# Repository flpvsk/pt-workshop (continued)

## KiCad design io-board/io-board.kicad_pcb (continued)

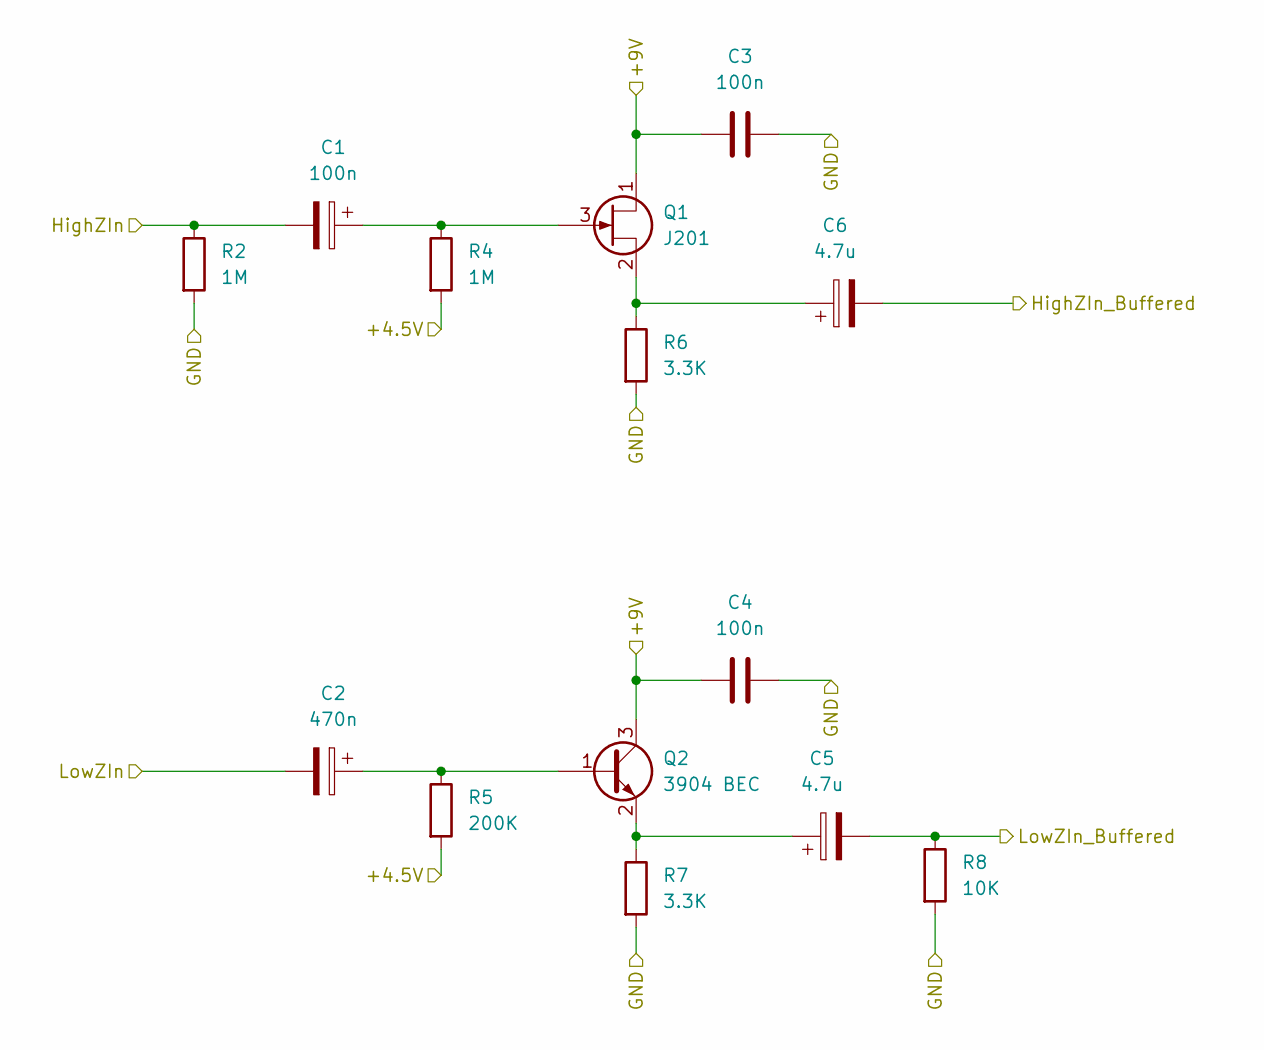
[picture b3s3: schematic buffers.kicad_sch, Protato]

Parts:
C1: 100n; CP_Elec_4x5.4; LCSC C271438
C2: 470n; CP_Elec_4x5.4; LCSC C305350
C3, C4: 100n; C_0603_1608Metric_Pad1.08x0.95mm_HandSolder; LCSC C497032
C5, C6: 4.7u; CP_Elec_4x5.4; Mouser 710-865080540002
Q1: J201; SOT-23_Handsoldering; LCSC C891687
Q2: 3904 BEC; SOT-23_Handsoldering; LCSC C20526
R2, R4: 1M; R_0603_1608Metric_Pad0.98x0.95mm_HandSolder; LCSC C105578
R5: 200K; R_0603_1608Metric_Pad0.98x0.95mm_HandSolder; LCSC C25811
R6, R7: 3.3K; R_0603_1608Metric_Pad0.98x0.95mm_HandSolder; LCSC C22978
R8: 10K; R_0603_1608Metric_Pad0.98x0.95mm_HandSolder; LCSC C25804

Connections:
/+4.5V: R4.2, R5.2; also elsewhere on the board
/Return: C2.2; also elsewhere on the board
/ReturnBuf: C5.2, R8.1; also elsewhere on the board
/Send: C1.2, R2.1; also elsewhere on the board
/SendBuf: C6.2; also elsewhere on the board
/Von: C3.1, C4.1, Q1.1 (D), Q2.3 (C); also elsewhere on the board
GND: C3.2, C4.2, R2.2, R6.2, R7.2, R8.2; also elsewhere on the board
unnamed: C1.1, Q1.3 (G), R4.1
unnamed: C2.1, Q2.1 (B), R5.1
unnamed: C5.1, Q2.2 (E), R7.1
unnamed: C6.1, Q1.2 (S), R6.1

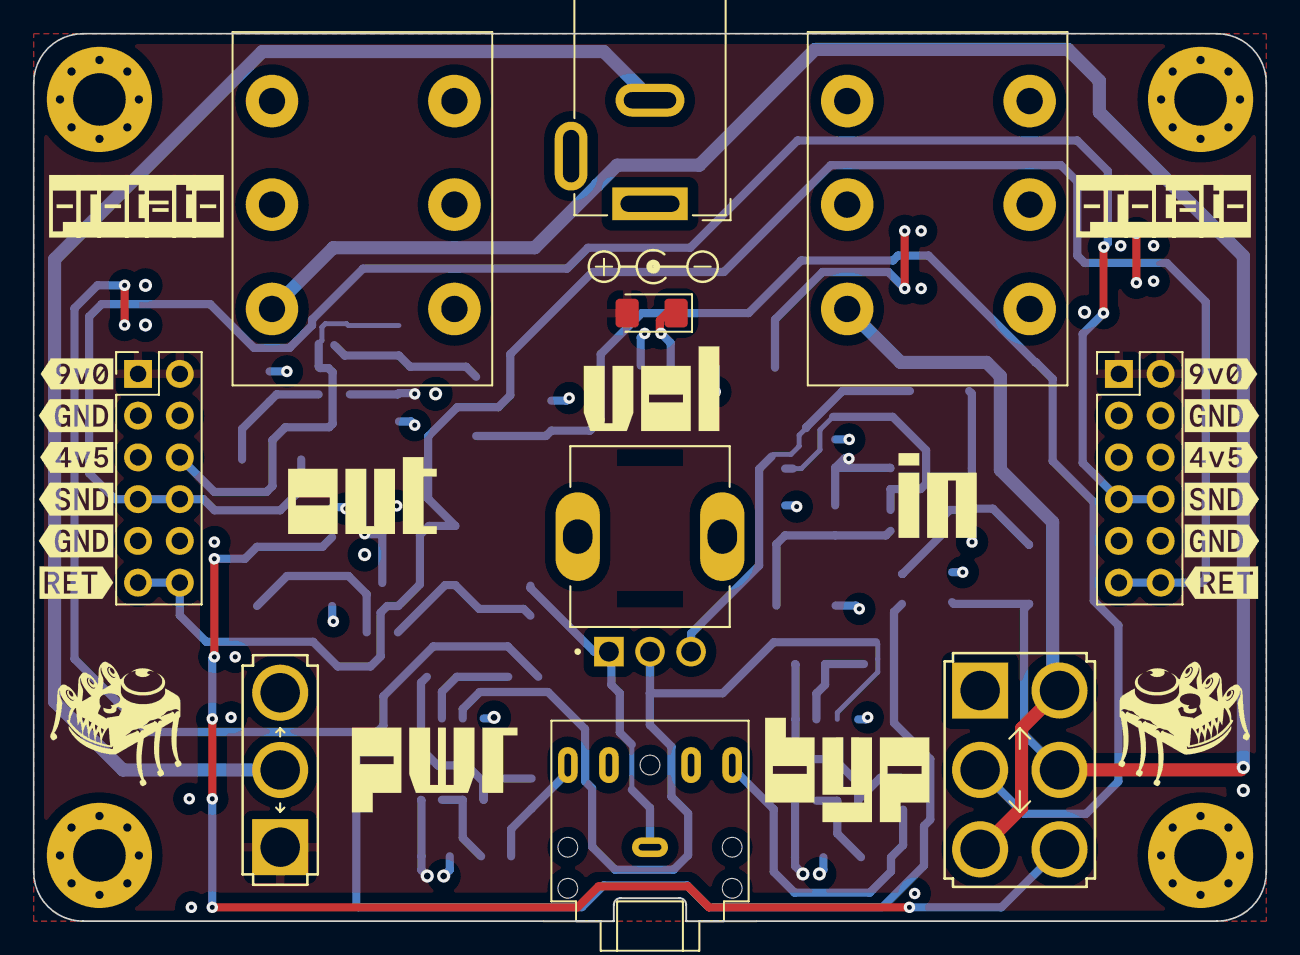
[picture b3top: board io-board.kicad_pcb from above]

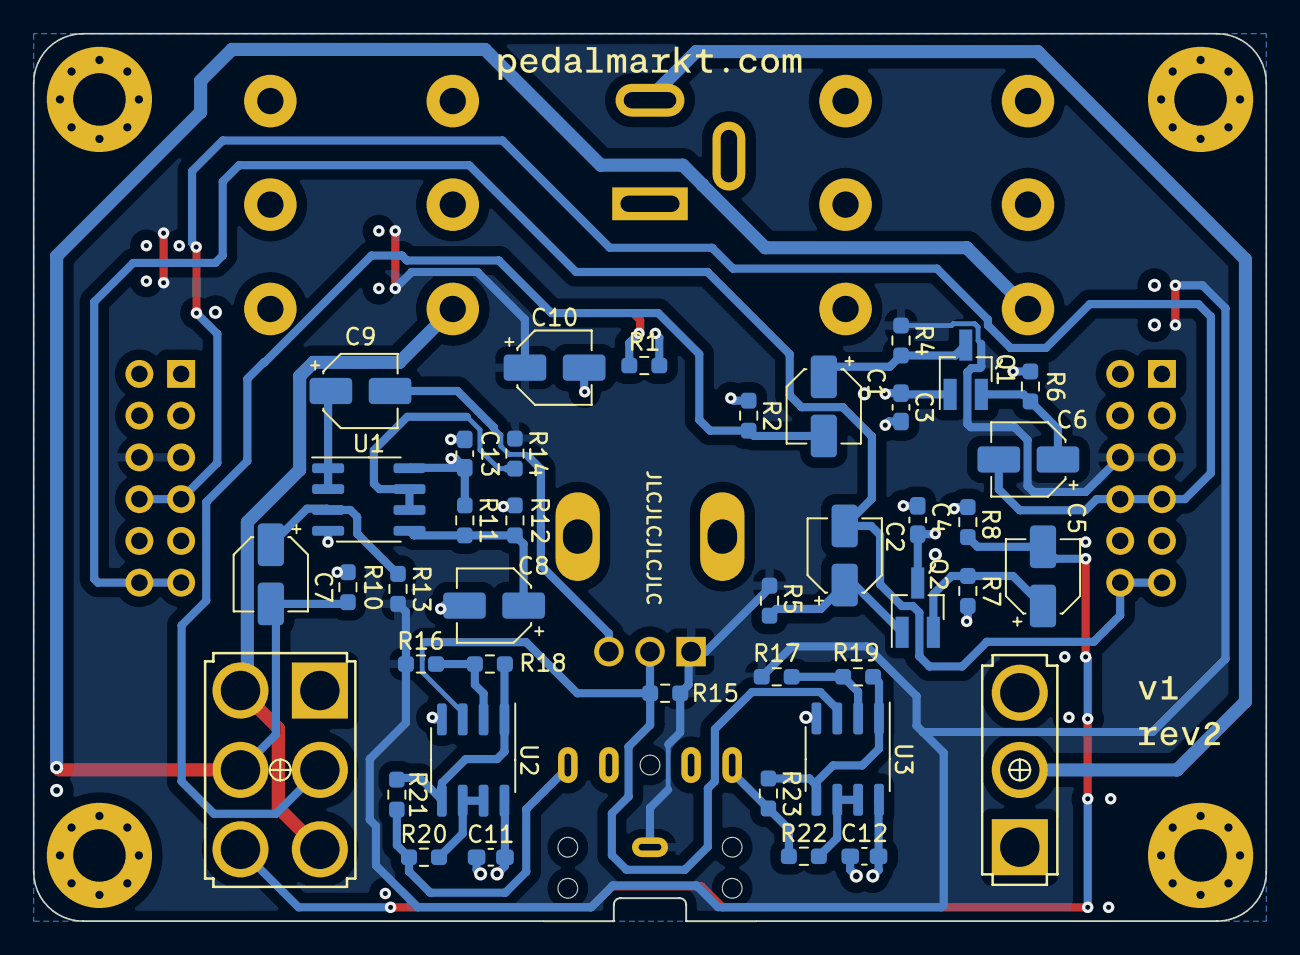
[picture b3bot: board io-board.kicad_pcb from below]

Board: 4 copper layers, 75.0 x 54.0 mm, 74 parts (41 on the bottom side), 29 nets.

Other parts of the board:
kibuzzard-65D7710E: G***; kibuzzard-65D7710E
kibuzzard-65D7712F: G***; kibuzzard-65D7712F
kibuzzard-65D7717A: G***; kibuzzard-65D7717A
kibuzzard-65D77151: G***; kibuzzard-65D77151
kibuzzard-65D77183: G***; kibuzzard-65D77183
kibuzzard-65D77819: G***; kibuzzard-65D77819
kibuzzard-65D77824: G***; kibuzzard-65D77824
kibuzzard-65DA328B: G***; kibuzzard-65DA328B
kibuzzard-672CB0D7: G***; kibuzzard-672CB0D7
kibuzzard-672CB0E4: G***; kibuzzard-672CB0E4
kibuzzard-672CB0EB: G***; kibuzzard-672CB0EB
kibuzzard-672CB0F3: G***; kibuzzard-672CB0F3
kibuzzard-672CB0F8: G***; kibuzzard-672CB0F8
kibuzzard-672CB03D: G***; kibuzzard-672CB03D
kibuzzard-672CB05C: G***; kibuzzard-672CB05C
kibuzzard-672CB16D: G***; kibuzzard-672CB16D
kibuzzard-672CB029: G***; kibuzzard-672CB029
kibuzzard-672CB033: G***; kibuzzard-672CB033
kibuzzard-672CB045: G***; kibuzzard-672CB045
kibuzzard-672CB052: G***; kibuzzard-672CB052
kibuzzard-672CB126: G***; kibuzzard-672CB126

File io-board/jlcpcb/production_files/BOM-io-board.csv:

Comment,Designator,Footprint,LCSC
1M,"R10,R13,R2,R4",R_0603_1608Metric_Pad0.98x0.95mm_HandSolder,C105578
3904 BEC,Q2,SOT-23_Handsoldering,C20526
1K,"R16,R17",R_0603_1608Metric_Pad0.98x0.95mm_HandSolder,C21190
10,R14,R_0603_1608Metric_Pad0.98x0.95mm_HandSolder,C22859
1R,"R20,R21,R22,R23",R_0603_1608Metric_Pad0.98x0.95mm_HandSolder,C22936
3.3K,"R6,R7",R_0603_1608Metric_Pad0.98x0.95mm_HandSolder,C22978
4.7K,"R1,R15",R_0603_1608Metric_Pad0.98x0.95mm_HandSolder,C23162
10u,"C10,C8",CP_Elec_4x5.4,C240540
10K,"R11,R12,R8",R_0603_1608Metric_Pad0.98x0.95mm_HandSolder,C25804
200K,R5,R_0603_1608Metric_Pad0.98x0.95mm_HandSolder,C25811
100n,"C1,C7,C9",CP_Elec_4x5.4,C271438
4.7u,"C5,C6",CP_Elec_4x5.4,C2963050
470n,C2,CP_Elec_4x5.4,C305350
2.2K,"R18,R19",R_0603_1608Metric_Pad0.98x0.95mm_HandSolder,C4190
100n,"C11,C12,C13,C3,C4",C_0603_1608Metric_Pad1.08x0.95mm_HandSolder,C497032
NE5532,"U2,U3",SOIC-8_3.9x4.9mm_P1.27mm,C7426
LM358,U1,SOIC-8_3.9x4.9mm_P1.27mm,C7950
PWRLED,D1,LED_1206_3216Metric_Pad1.42x1.75mm_HandSolder,C84256
J201,Q1,SOT-23_Handsoldering,C891687
PWRSW,SW2,SPDT.LUGS,
SignalSW,SW1,DPDT.LUGS,
Out,J6,tayda-6mm35-jack-pcb-compact,
BL,H3,MountingHole_3.2mm_M3_Pad_Via,
In,J5,tayda-6mm35-jack-pcb-compact,
BR,H4,MountingHole_3.2mm_M3_Pad_Via,
Headphone,J7,Jack_3.5mm_CUI_SJ1-3525N_Horizontal,
Conn,J8,PinHeader_2x06_P2.54mm_Vertical,
PWR,J4,BarrelJack_GCT_DCJ200-10-A_Horizontal,
TL,H1,MountingHole_3.2mm_M3_Pad_Via,
A20K,RV1,V3_TRIM_R0904NB10KL-Keepout,
Conn,J3,PinHeader_2x06_P2.54mm_Vertical,
TR,H2,MountingHole_3.2mm_M3_Pad_Via,

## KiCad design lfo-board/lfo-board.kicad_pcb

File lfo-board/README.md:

### Longwave

[StompLFO][stomplfo] breadboard-friendly adapter board that
provides power to the chip and shifts control and output
voltages to be in the [2V, 7V] range that is more
pedal-friendly than [0V, 5V].

[stomplfo]: https://electricdruid.net/product/stomplfo/

[Schematic](./longwave-v1rev2.pdf)

#### Pins

1. +9V (Input)
2. GND (Input)
3. +4.5 (Input)
4. +5.0V (Output of the on-board 5V regulator)
5. GND (Input)
6. Out (Output of the LFO)
7. GND (Input)
8. Sync (Input, external clock signal to sync LFO to)
9. Tap (Input, tap tempo, connect to GND for tap)
10. Vfreq (Input, CV for LFO speed)
11. Vof (Input, CV for LFO offset)
12. GND (Input)
13. Vform (Input, CV for LFO waveshape)
14. Vdepth (Input, CV for LFO depth)
15. GND (Input)

For minimum operation, please connect these pins. Keep in
mind for duplicate pins like GND, it's sufficient to just
connect one of the pins.

* `Pin 1`: +9V;
* `Pin 2`: GND;
* `Pin 3`: +4.5V;
* `Pin 6`: LFO Out;

#### Control Voltage ranges

All CV inputs are effective on the [2V, 7V] range. They are
also clamped in a way that it is safe to use the full [0V,
9V] range.

* `Vfreq`: 2V corresponds to ~25Hz LFO frequency, 7V to
  ~50mHz;
* `Vof`: 2V corresponds to an offset of +2.5V on the LFO
  output (LFO will "oscillate" around 7V). 7V corresponds to
  -2.5V offset; to 0V peak-to-peak, effectively a constant
* `Vdepth`: 2V corresponds to 5V peak-to-peak LFO output, 7V
  to 0V peak-to-peak, effectively a constant voltage
  reference controlled by `Vof`
  voltage reference controlled by `Vof`
* `Vform`: controls the waveshape of the LFO. Approximate
  ranges:
    * [0V, 2.8V) - smooth random
    * [2.8V, 3.4V) - stepped random
    * [3.4V, 4.2V) - sweep
    * [4.2V, 4.8V) - triangle
    * [4.8V, 5.4V) - square
    * [5.4V, 6.7V) - ramp down
    * [6.7V, 7.0V) - ramp up

The easiest way to get control voltage for each of the
inputs is with a B10k potentiometer:

![Drawing of a potentiometer, pin one connected to 9V, pin
three to GND, pin 2 goes to CV In](./img/cv-pot.png)

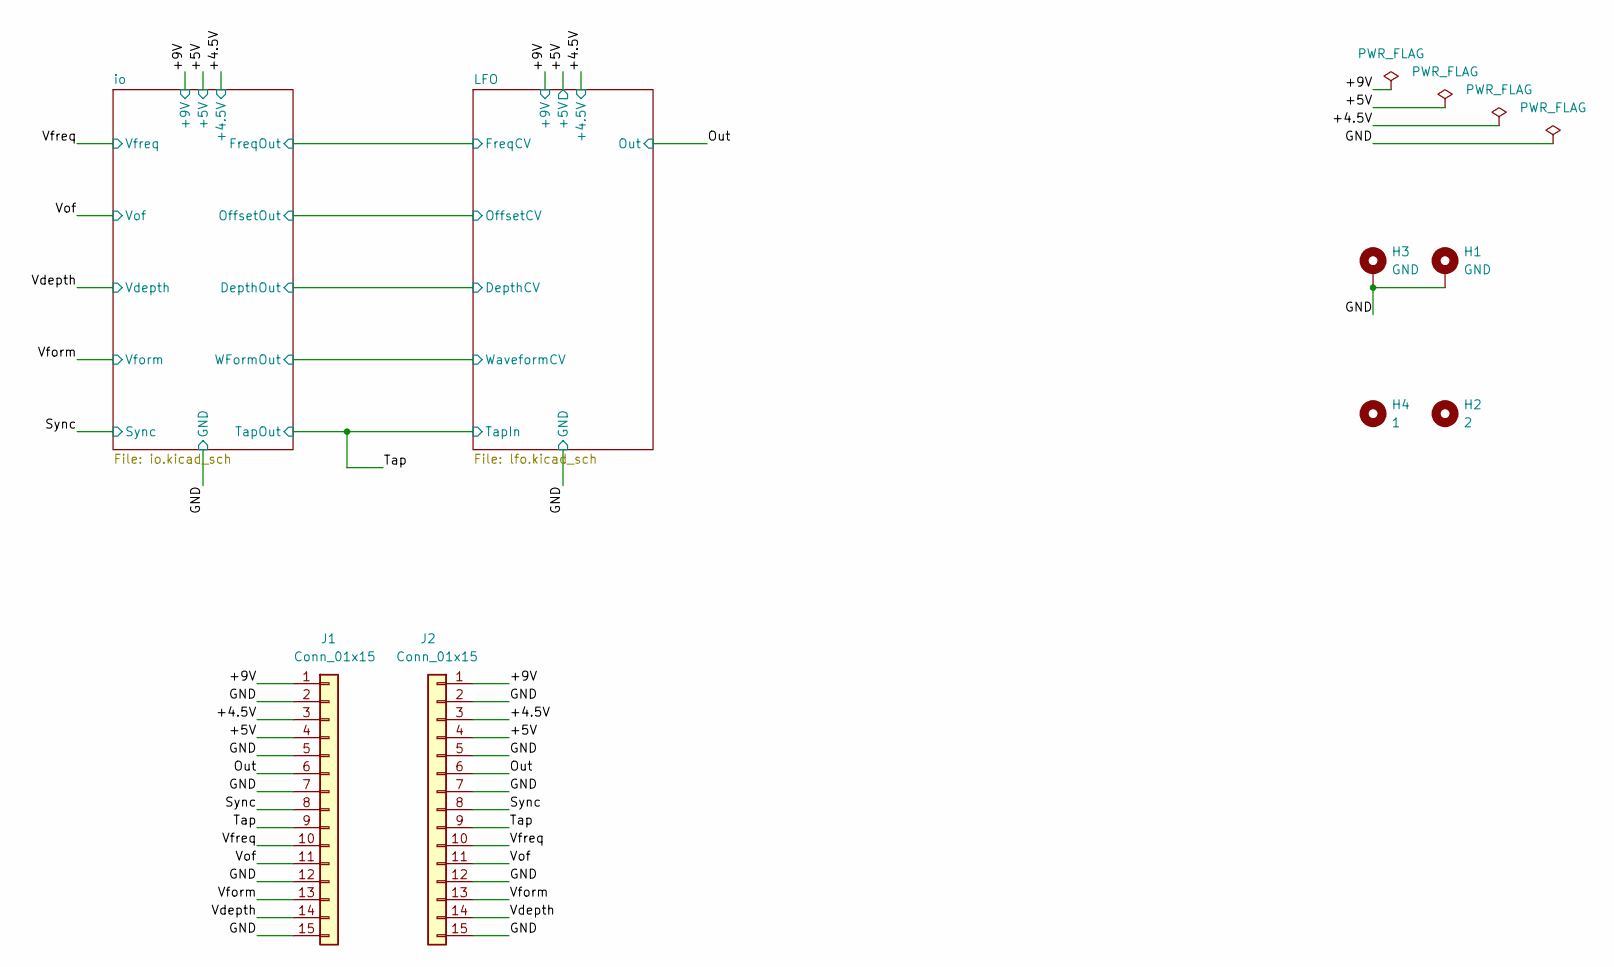
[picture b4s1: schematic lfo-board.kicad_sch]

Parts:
H1, H3: GND; MountingHole_3.2mm_M3_ISO14580_Pad
H2: 2; MountingHole_3.2mm_M3
H4: 1; MountingHole_3.2mm_M3
J1, J2: Conn_01x15; PinSocket_1x15_P2.54mm_Vertical

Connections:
/+4.5V: J1.3, J2.3; also elsewhere on the board
/+5V: J1.4, J2.4; also elsewhere on the board
/+9V: J1.1, J2.1; also elsewhere on the board
/GND: H1.1, H3.1, J1.2, J1.5, J1.7, J1.12, J1.15, J2.2, J2.5, J2.7, J2.12, J2.15; also elsewhere on the board
/Out: J1.6, J2.6; also elsewhere on the board
/Sync: J1.8, J2.8; also elsewhere on the board
/Tap: J1.9, J2.9; also elsewhere on the board
/Vdepth: J1.14, J2.14; also elsewhere on the board
/Vform: J1.13, J2.13; also elsewhere on the board
/Vfreq: J1.10, J2.10; also elsewhere on the board
/Vof: J1.11, J2.11; also elsewhere on the board

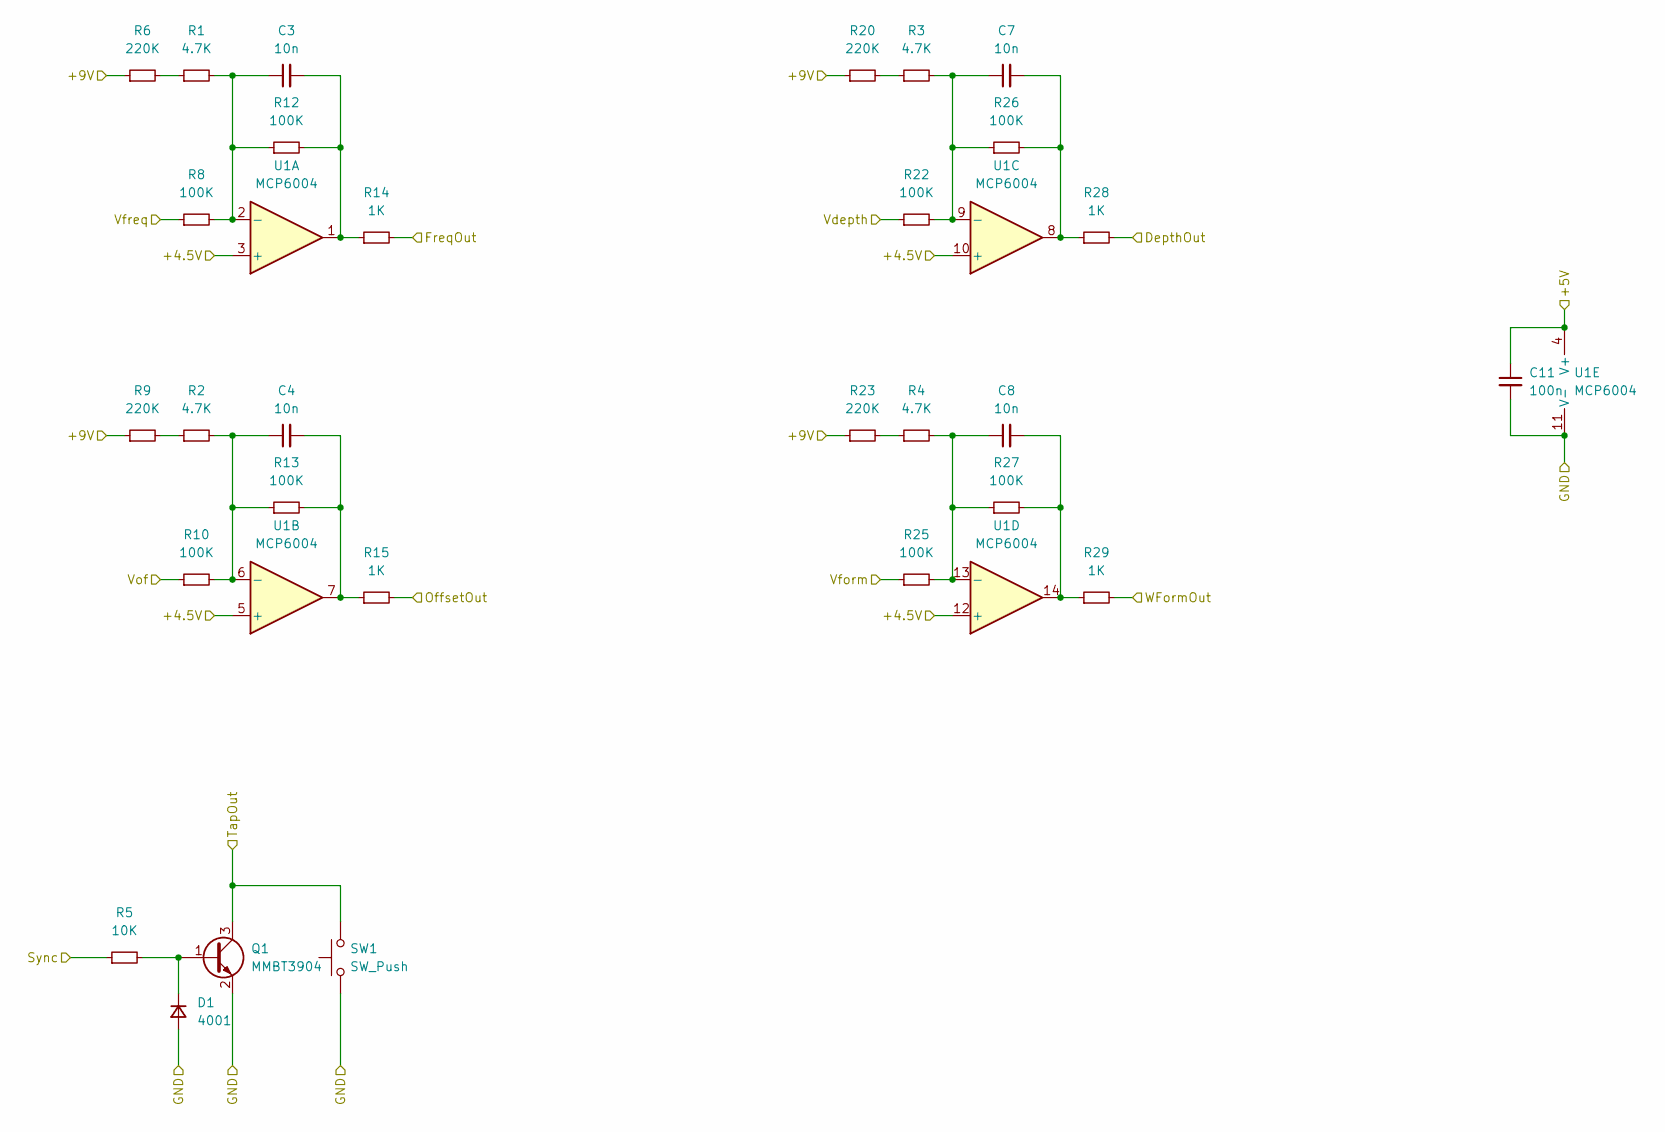
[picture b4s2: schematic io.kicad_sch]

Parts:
C3, C4, C7, C8: 10n; C_0603_1608Metric_Pad1.08x0.95mm_HandSolder; LCSC C57112
C11: 100n; C_0603_1608Metric_Pad1.08x0.95mm_HandSolder; LCSC C497032
D1: 4001; D_SMA_Handsoldering; LCSC C122841
Q1: MMBT3904; SOT-23; LCSC C20526
R1, R2, R3, R4: 4.7K; R_0603_1608Metric_Pad0.98x0.95mm_HandSolder; LCSC C23162
R5: 10K; R_0603_1608Metric_Pad0.98x0.95mm_HandSolder; LCSC C25804
R6, R9, R20, R23: 220K; R_0603_1608Metric_Pad0.98x0.95mm_HandSolder; LCSC C22961
R8, R10, R12, R13, R22, R25, R26, R27: 100K; R_0603_1608Metric_Pad0.98x0.95mm_HandSolder; LCSC C25803
R14, R15, R28, R29: 1K; R_0603_1608Metric_Pad0.98x0.95mm_HandSolder; LCSC C21190
SW1: SW_Push; SW_Push_SPST_NO_Alps_SKRK; LCSC C455280
U1: MCP6004; SOIC-14_3.9x8.7mm_P1.27mm; LCSC C7378

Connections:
/+4.5V: U1.3 (+), U1.5 (+), U1.10 (+), U1.12 (+); also elsewhere on the board
/+5V: C11.1, U1.4 (V+); also elsewhere on the board
/+9V: R6.1, R9.1, R20.1, R23.1; also elsewhere on the board
/GND: C11.2, D1.2 (A), Q1.2 (E), SW1.1, U1.11 (V-); also elsewhere on the board
/LFO/DepthCV: R28.2; also elsewhere on the board
/LFO/FreqCV: R14.2; also elsewhere on the board
/LFO/OffsetCV: R15.2; also elsewhere on the board
/LFO/WaveformCV: R29.2; also elsewhere on the board
/Sync: R5.1; also elsewhere on the board
/Tap: Q1.3 (C), SW1.2; also elsewhere on the board
/Vdepth: R22.1; also elsewhere on the board
/Vform: R25.1; also elsewhere on the board
/Vfreq: R8.1; also elsewhere on the board
/Vof: R10.1; also elsewhere on the board
unnamed: C3.1, R1.2, R8.2, R12.1, U1.2 (-)
unnamed: C3.2, R12.2, R14.1, U1.1
unnamed: C4.1, R2.2, R10.2, R13.1, U1.6 (-)
unnamed: C4.2, R13.2, R15.1, U1.7
unnamed: C7.1, R3.2, R22.2, R26.1, U1.9 (-)
unnamed: C7.2, R26.2, R28.1, U1.8
unnamed: C8.1, R4.2, R25.2, R27.1, U1.13 (-)
unnamed: C8.2, R27.2, R29.1, U1.14
unnamed: D1.1 (K), Q1.1 (B), R5.2
unnamed: R1.1, R6.2
unnamed: R2.1, R9.2
unnamed: R3.1, R20.2
unnamed: R4.1, R23.2

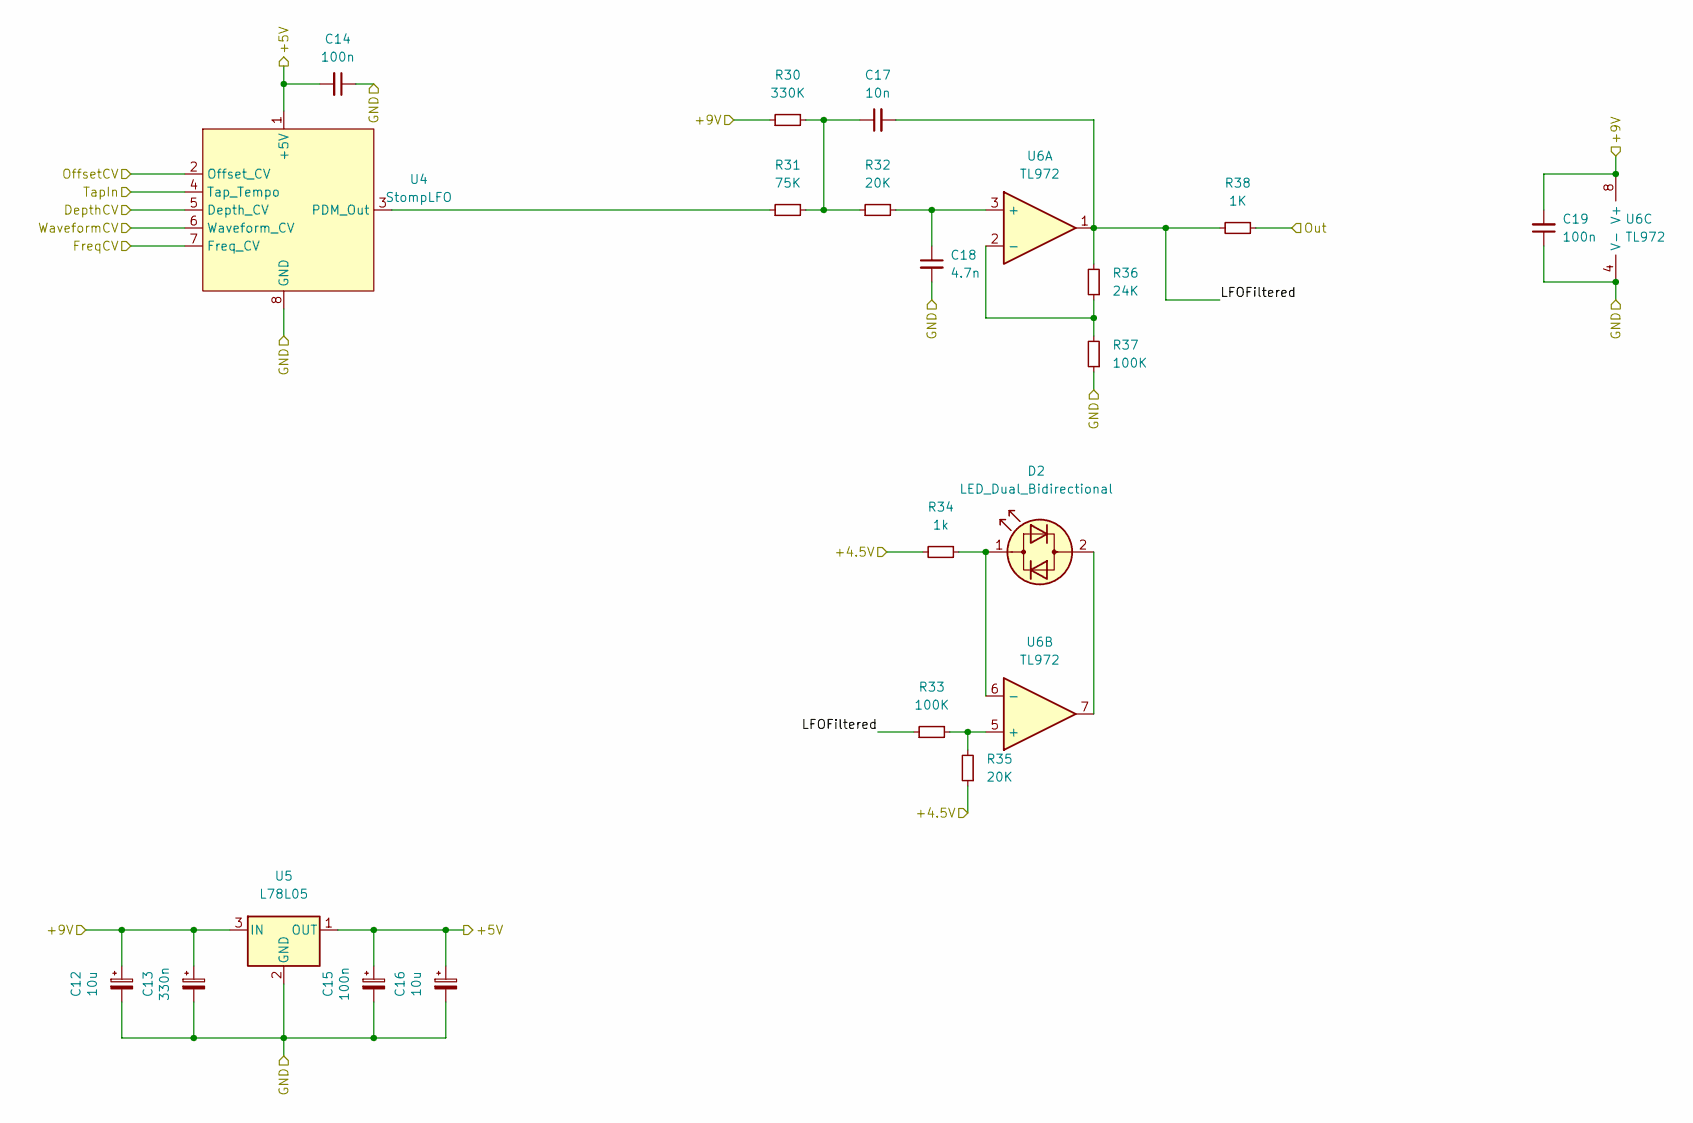
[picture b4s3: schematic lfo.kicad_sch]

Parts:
C12, C16: 10u; CP_EIA-3216-10_Kemet-I_Pad1.58x1.35mm_HandSolder; LCSC C128254
C13: 330n; CP_EIA-3216-10_Kemet-I_Pad1.58x1.35mm_HandSolder; LCSC C212667
C14, C19: 100n; C_0603_1608Metric_Pad1.08x0.95mm_HandSolder; LCSC C497032
C15: 100n; CP_EIA-3216-10_Kemet-I_Pad1.58x1.35mm_HandSolder; LCSC C7173
C17: 10n; C_0603_1608Metric_Pad1.08x0.95mm_HandSolder; LCSC C57112
C18: 4.7n; C_0603_1608Metric_Pad1.08x0.95mm_HandSolder; LCSC C85980
D2: LED_Dual_Bidirectional; LED_D3.0mm
R30: 330K; R_0603_1608Metric_Pad0.98x0.95mm_HandSolder; LCSC C23137
R31: 75K; R_0603_1608Metric_Pad0.98x0.95mm_HandSolder; LCSC C23242
R32, R35: 20K; R_0603_1608Metric_Pad0.98x0.95mm_HandSolder; LCSC C4184
R33, R37: 100K; R_0603_1608Metric_Pad0.98x0.95mm_HandSolder; LCSC C25803
R34: 1k; R_0603_1608Metric_Pad0.98x0.95mm_HandSolder; LCSC C21190
R36: 24K; R_0603_1608Metric_Pad0.98x0.95mm_HandSolder; LCSC C23352
R38: 1K; R_0603_1608Metric_Pad0.98x0.95mm_HandSolder; LCSC C21190
U4: StompLFO; SOIC-8_3.9x4.9mm_P1.27mm
U5: L78L05; SOT-89-3; LCSC C347258
U6: TL972; SOIC-8_3.9x4.9mm_P1.27mm; LCSC C46127

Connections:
/+4.5V: R34.2, R35.1; also elsewhere on the board
/+5V: C14.2, C15.1, C16.1, U4.1 (+5V), U5.1 (OUT); also elsewhere on the board
/+9V: C12.1, C13.1, C19.2, R30.1, U5.3 (IN), U6.8 (V+); also elsewhere on the board
/GND: C12.2, C13.2, C14.1, C15.2, C16.2, C18.2, C19.1, R37.1, U4.8 (GND), U5.2 (GND), U6.4 (V-); also elsewhere on the board
/LFO/DepthCV: U4.5 (Depth_CV); also elsewhere on the board
/LFO/FreqCV: U4.7 (Freq_CV); also elsewhere on the board
/LFO/LFOFiltered: C17.2, R33.1, R36.2, R38.2, U6.1
/LFO/OffsetCV: U4.2 (Offset_CV); also elsewhere on the board
/LFO/WaveformCV: U4.6 (Waveform_CV); also elsewhere on the board
/Out: R38.1; also elsewhere on the board
/Tap: U4.4 (Tap_Tempo); also elsewhere on the board
unnamed: C17.1, R30.2, R31.2, R32.1
unnamed: C18.1, R32.2, U6.3 (+)
unnamed: D2.1 (KA), R34.1, U6.6 (-)
unnamed: D2.2 (AK), U6.7
unnamed: R31.1, U4.3 (PDM_Out)
unnamed: R33.2, R35.2, U6.5 (+)
unnamed: R36.1, R37.2, U6.2 (-)

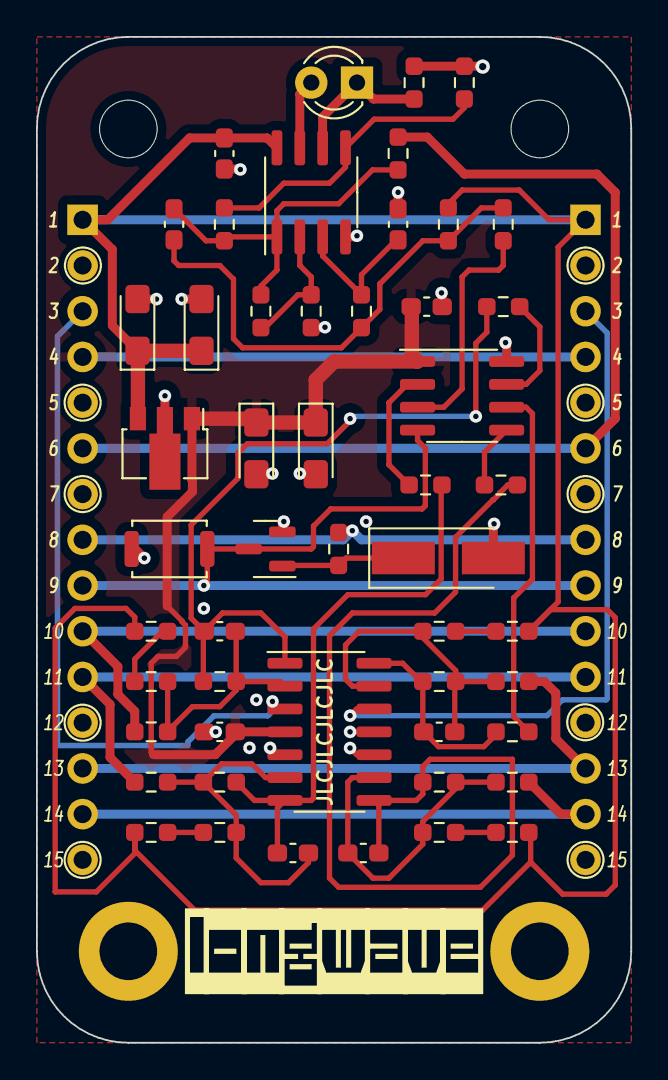
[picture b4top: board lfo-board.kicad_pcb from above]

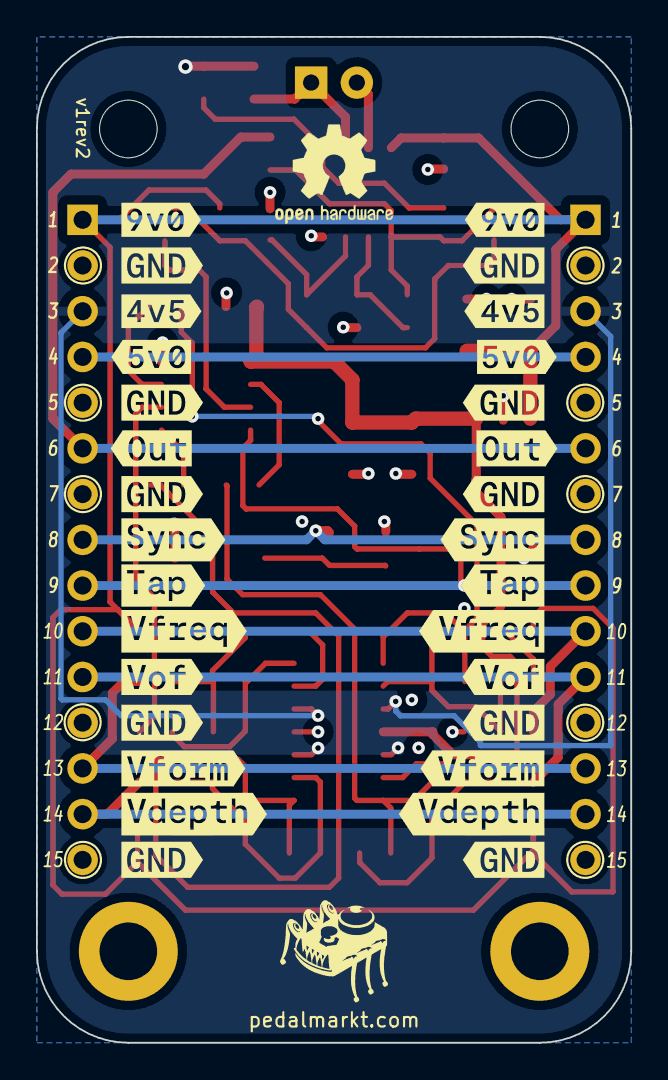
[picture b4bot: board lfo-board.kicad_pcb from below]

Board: 4 copper layers, 33.0 x 55.9 mm, 88 parts (30 on the bottom side), 36 nets.

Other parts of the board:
kibuzzard-65FC6621: G***; kibuzzard-65FC6621
kibuzzard-672CB4A3: G***; kibuzzard-672CB4A3
kibuzzard-672CB4B5: G***; kibuzzard-672CB4B5
kibuzzard-672CB4C0: G***; kibuzzard-672CB4C0
kibuzzard-672CB4C9: G***; kibuzzard-672CB4C9
kibuzzard-672CB4D2: G***; kibuzzard-672CB4D2
kibuzzard-672CB4D9: G***; kibuzzard-672CB4D9
kibuzzard-672CB5A6: G***; kibuzzard-672CB5A6
kibuzzard-672CB5AE: G***; kibuzzard-672CB5AE
kibuzzard-672CB5B5: G***; kibuzzard-672CB5B5
kibuzzard-672CB5BD: G***; kibuzzard-672CB5BD
kibuzzard-672CB5CA: G***; kibuzzard-672CB5CA
kibuzzard-672CB5D3: G***; kibuzzard-672CB5D3
kibuzzard-672CB5DA: G***; kibuzzard-672CB5DA
kibuzzard-672CB5E3: G***; kibuzzard-672CB5E3
kibuzzard-672CB5EB: G***; kibuzzard-672CB5EB
kibuzzard-672CB5F6: G***; kibuzzard-672CB5F6
kibuzzard-672CB5FF: G***; kibuzzard-672CB5FF
kibuzzard-672CB46D: G***; kibuzzard-672CB46D
kibuzzard-672CB47A: G***; kibuzzard-672CB47A
kibuzzard-672CB47E: G***; kibuzzard-672CB47E
kibuzzard-672CB48C: G***; kibuzzard-672CB48C
kibuzzard-672CB59C: G***; kibuzzard-672CB59C
kibuzzard-672CB60E: G***; kibuzzard-672CB60E
kibuzzard-672CB471: G***; kibuzzard-672CB471
kibuzzard-672CB474: G***; kibuzzard-672CB474
kibuzzard-672CB484: G***; kibuzzard-672CB484
kibuzzard-672CB488: G***; kibuzzard-672CB488
kibuzzard-672CB496: G***; kibuzzard-672CB496
kibuzzard-672CB606: G***; kibuzzard-672CB606
kibuzzard-672CB614: G***; kibuzzard-672CB614

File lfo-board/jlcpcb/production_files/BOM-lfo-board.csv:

Comment,Designator,Footprint,LCSC
4001,D1,D_SMA_Handsoldering,C122841
10u,"C12,C16",CP_EIA-3216-10_Kemet-I_Pad1.58x1.35mm_HandSolder,C128254
MMBT3904,Q1,SOT-23,C20526
1K,"R14,R15,R28,R29,R34,R38",R_0603_1608Metric_Pad0.98x0.95mm_HandSolder,C21190
330n,C13,CP_EIA-3216-10_Kemet-I_Pad1.58x1.35mm_HandSolder,C212667
220K,"R20,R23,R6,R9",R_0603_1608Metric_Pad0.98x0.95mm_HandSolder,C22961
330K,R30,R_0603_1608Metric_Pad0.98x0.95mm_HandSolder,C23137
4.7K,"R1,R2,R3,R4",R_0603_1608Metric_Pad0.98x0.95mm_HandSolder,C23162
75K,R31,R_0603_1608Metric_Pad0.98x0.95mm_HandSolder,C23242
24K,R36,R_0603_1608Metric_Pad0.98x0.95mm_HandSolder,C23352
100K,"R10,R12,R13,R22,R25,R26,R27,R33,R37,R8",R_0603_1608Metric_Pad0.98x0.95mm_HandSolder,C25803
10K,R5,R_0603_1608Metric_Pad0.98x0.95mm_HandSolder,C25804
L78L05,U5,SOT-89-3,C347258
20K,"R32,R35",R_0603_1608Metric_Pad0.98x0.95mm_HandSolder,C4184
SW_Push,SW1,SW_Push_SPST_NO_Alps_SKRK,C455280
TL972,U6,SOIC-8_3.9x4.9mm_P1.27mm,C46127
100n,"C11,C14,C19",C_0603_1608Metric_Pad1.08x0.95mm_HandSolder,C497032
10n,"C17,C3,C4,C7,C8",C_0603_1608Metric_Pad1.08x0.95mm_HandSolder,C57112
100n,C15,CP_EIA-3216-10_Kemet-I_Pad1.58x1.35mm_HandSolder,C7173
MCP6004,U1,SOIC-14_3.9x8.7mm_P1.27mm,C7378
4.7n,C18,C_0603_1608Metric_Pad1.08x0.95mm_HandSolder,C85980
GND,H1,MountingHole_3.2mm_M3_ISO14580_Pad,
2,H2,MountingHole_3.2mm_M3,
StompLFO,U4,SOIC-8_3.9x4.9mm_P1.27mm,
LED_Dual_Bidirectional,D2,LED_D3.0mm,
GND,H3,MountingHole_3.2mm_M3_ISO14580_Pad,
Conn_01x15,J2,PinSocket_1x15_P2.54mm_Vertical,
1,H4,MountingHole_3.2mm_M3,
Conn_01x15,J1,PinSocket_1x15_P2.54mm_Vertical,

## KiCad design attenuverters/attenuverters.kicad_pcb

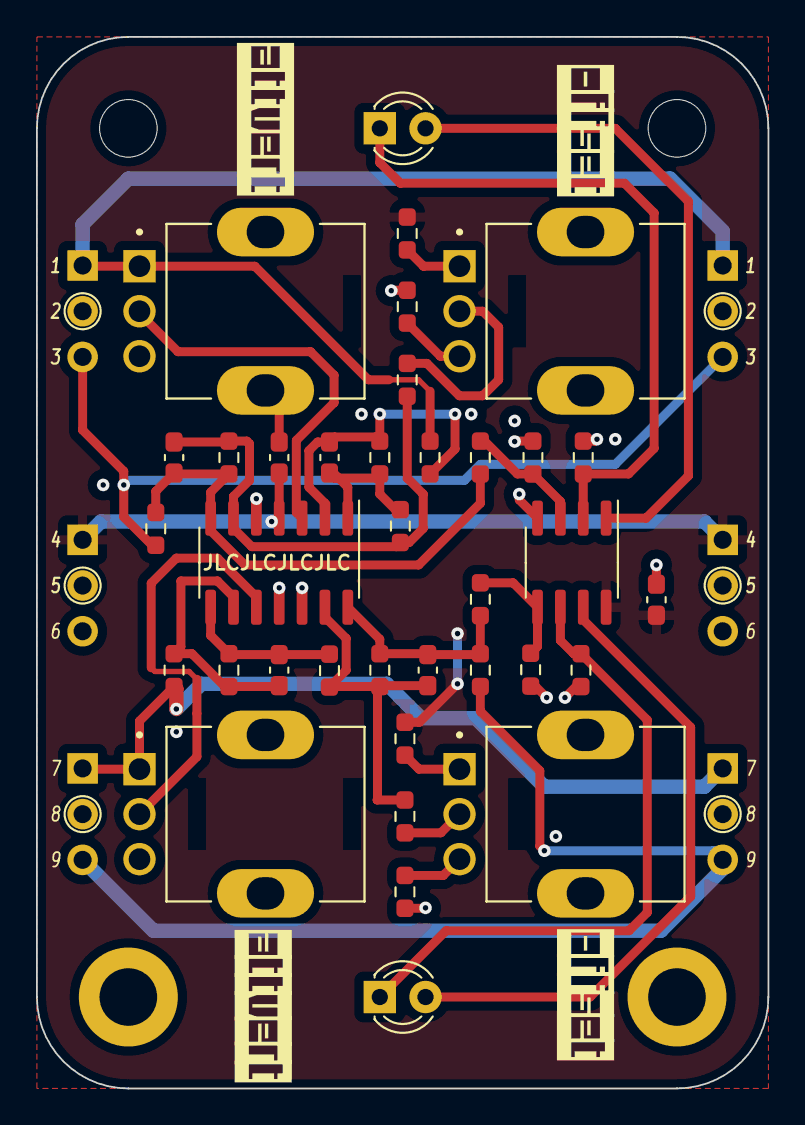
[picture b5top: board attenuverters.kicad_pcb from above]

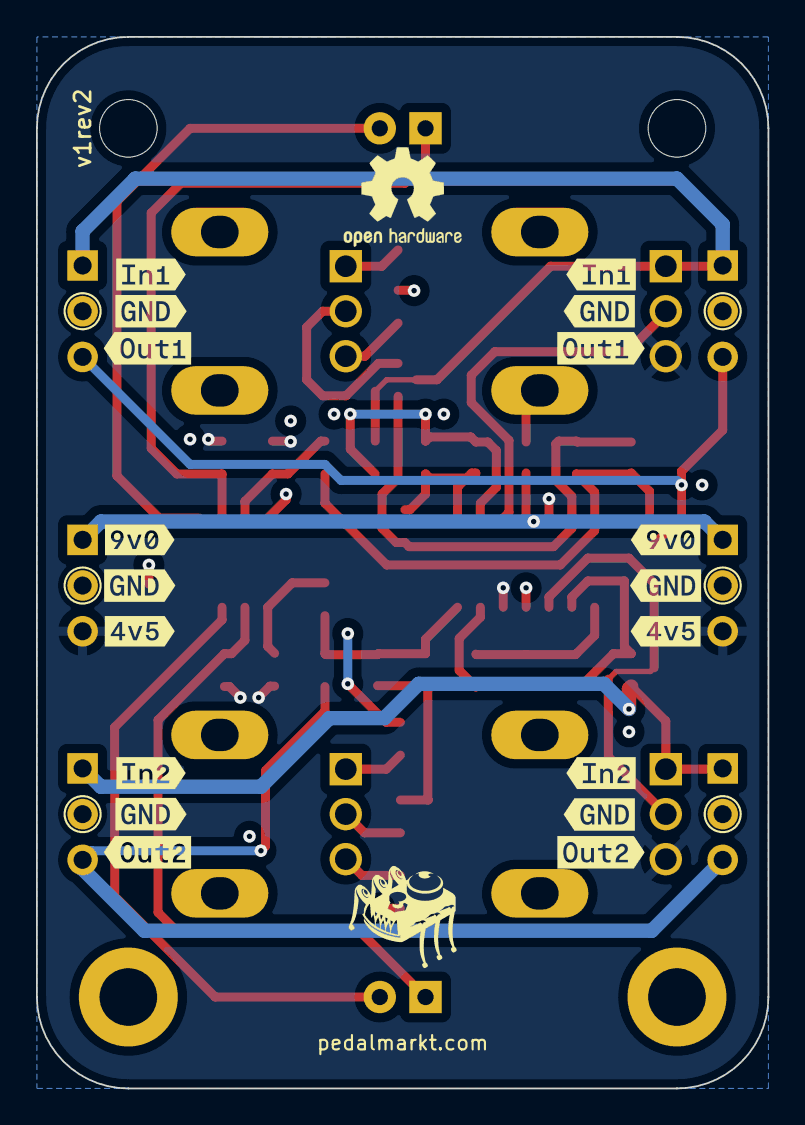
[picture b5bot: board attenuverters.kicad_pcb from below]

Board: 4 copper layers, 40.6 x 58.4 mm, 68 parts (18 on the bottom side), 29 nets.

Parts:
C1, C2, C3, C4: 10p; C_0603_1608Metric_Pad1.08x0.95mm_HandSolder
C5, C6: 100n; C_0603_1608Metric_Pad1.08x0.95mm_HandSolder
D1, D2: LED_Dual_Bidirectional; LED_D3.0mm
H1, H3: GND; MountingHole_3.2mm_M3_ISO14580_Pad
H2: 1; MountingHole_3.2mm_M3
H4: 2; MountingHole_3.2mm_M3
J1: C1; PinSocket_1x03_P2.54mm_Vertical
J2: C3; PinSocket_1x03_P2.54mm_Vertical
J3: C5; PinSocket_1x03_P2.54mm_Vertical
J4: C2; PinSocket_1x03_P2.54mm_Vertical
J5: C4; PinSocket_1x03_P2.54mm_Vertical
J6: C6; PinSocket_1x03_P2.54mm_Vertical
R1, R2, R3, R4, R9, R10, R11, R12, R13, R14, R18, R20: 100K; R_0603_1608Metric_Pad0.98x0.95mm_HandSolder
R5, R6, R7, R8, R15, R16, R17, R19: 1K; R_0603_1608Metric_Pad0.98x0.95mm_HandSolder
R21, R22: 20K; R_0603_1608Metric_Pad0.98x0.95mm_HandSolder
RV1, RV2, RV3, RV4: B100K; V3_TRIM_R0904NB10KL-Keepout
U1: OPA4991; SOIC-14_3.9x8.7mm_P1.27mm
U2: TL072; SOIC-8_3.9x4.9mm_P1.27mm
kibuzzard-65FD570C, kibuzzard-65FD570C#2: G***; kibuzzard-65FD570C
kibuzzard-65FD5706, kibuzzard-65FD5706#2: G***; kibuzzard-65FD5706
kibuzzard-672CA9D7: G***; kibuzzard-672CA9D7
kibuzzard-672CA9E5: G***; kibuzzard-672CA9E5
kibuzzard-672CA9F1: G***; kibuzzard-672CA9F1
kibuzzard-672CAA1B: G***; kibuzzard-672CAA1B
kibuzzard-672CAA2D: G***; kibuzzard-672CAA2D
kibuzzard-672CAA4A: G***; kibuzzard-672CAA4A
kibuzzard-672CAA5E: G***; kibuzzard-672CAA5E
kibuzzard-672CAA17: G***; kibuzzard-672CAA17
kibuzzard-672CAA21: G***; kibuzzard-672CAA21
kibuzzard-672CAA28: G***; kibuzzard-672CAA28
kibuzzard-672CAA31: G***; kibuzzard-672CAA31
kibuzzard-672CAA40: G***; kibuzzard-672CAA40
kibuzzard-672CAA46: G***; kibuzzard-672CAA46
kibuzzard-672CAA50: G***; kibuzzard-672CAA50
kibuzzard-672CAA54: G***; kibuzzard-672CAA54
kibuzzard-672CAA58: G***; kibuzzard-672CAA58
kibuzzard-672CAA64: G***; kibuzzard-672CAA64
kibuzzard-672CAA68: G***; kibuzzard-672CAA68

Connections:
/+4.5V: J2.3, J5.3, R17.2, R19.2, R21.2, R22.2, RV1.3, RV2.3, U1.5 (+), U1.12 (+)
/+9V: C5.1, C6.1, J2.1, J5.1, R5.1, R7.2, U1.4 (V+), U2.8 (V+)
/GND: C5.2, C6.2, H1.1, H3.1, J1.2, J2.2, J3.2, J4.2, J5.2, J6.2, R6.2, R8.2, RV1.0 (ShieldPin), RV2.0 (ShieldPin), RV3.0 (ShieldPin), RV4.0 (ShieldPin), U1.11 (V-), U2.4 (V-)
/In1: J1.1, J4.1, R1.1, RV1.1
/In2: J3.1, J6.1, R2.1, RV2.1
/Out1: J1.3, J4.3, R15.1
/Out2: J3.3, J6.3, R16.1
unnamed: C1.1, R1.2, R3.2, U1.2 (-)
unnamed: C1.2, R3.1, R10.2, U1.1
unnamed: C2.1, R2.2, R4.2, U1.9 (-)
unnamed: C2.2, R4.1, R12.2, U1.8
unnamed: C3.1, R9.1, R10.1, R13.2, U1.6 (-)
unnamed: C3.2, R13.1, R15.2, R18.2, U1.7
unnamed: C4.1, R11.1, R12.1, R14.2, U1.13 (-)
unnamed: C4.2, R14.1, R16.2, R20.2, U1.14
unnamed: D1.1 (KA), R17.1, U2.2 (-)
unnamed: D1.2 (AK), U2.1
unnamed: D2.1 (KA), R19.1, U2.6 (-)
unnamed: D2.2 (AK), U2.7
unnamed: R5.2, RV3.1
unnamed: R6.1, RV3.3
unnamed: R7.1, RV4.1
unnamed: R8.1, RV4.3
unnamed: R9.2, RV3.2
unnamed: R11.2, RV4.2
unnamed: R18.1, R21.1, U2.3 (+)
unnamed: R20.1, R22.1, U2.5 (+)
unnamed: RV1.2, U1.3 (+)
unnamed: RV2.2, U1.10 (+)

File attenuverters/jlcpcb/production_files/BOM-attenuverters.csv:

Comment,Designator,Footprint,LCSC
1K,"R15,R16,R17,R19,R5,R6,R7,R8",R_0603_1608Metric_Pad0.98x0.95mm_HandSolder,C21190
100K,"R1,R10,R11,R12,R13,R14,R18,R2,R20,R3,R4,R9",R_0603_1608Metric_Pad0.98x0.95mm_HandSolder,C25803
OPA4991,U1,SOIC-14_3.9x8.7mm_P1.27mm,C2860973
20K,"R21,R22",R_0603_1608Metric_Pad0.98x0.95mm_HandSolder,C4184
100n,"C5,C6",C_0603_1608Metric_Pad1.08x0.95mm_HandSolder,C497032
TL072,U2,SOIC-8_3.9x4.9mm_P1.27mm,C6961
10p,"C1,C2,C3,C4",C_0603_1608Metric_Pad1.08x0.95mm_HandSolder,C91367
LED_Dual_Bidirectional,D2,LED_D3.0mm,
LED_Dual_Bidirectional,D1,LED_D3.0mm,
C1,J1,PinSocket_1x03_P2.54mm_Vertical,
B100K,RV3,V3_TRIM_R0904NB10KL-Keepout,
B100K,RV1,V3_TRIM_R0904NB10KL-Keepout,
1,H2,MountingHole_3.2mm_M3,
C3,J2,PinSocket_1x03_P2.54mm_Vertical,
C6,J6,PinSocket_1x03_P2.54mm_Vertical,
B100K,RV2,V3_TRIM_R0904NB10KL-Keepout,
C4,J5,PinSocket_1x03_P2.54mm_Vertical,
GND,H1,MountingHole_3.2mm_M3_ISO14580_Pad,
C5,J3,PinSocket_1x03_P2.54mm_Vertical,
C2,J4,PinSocket_1x03_P2.54mm_Vertical,
GND,H3,MountingHole_3.2mm_M3_ISO14580_Pad,
2,H4,MountingHole_3.2mm_M3,
B100K,RV4,V3_TRIM_R0904NB10KL-Keepout,
